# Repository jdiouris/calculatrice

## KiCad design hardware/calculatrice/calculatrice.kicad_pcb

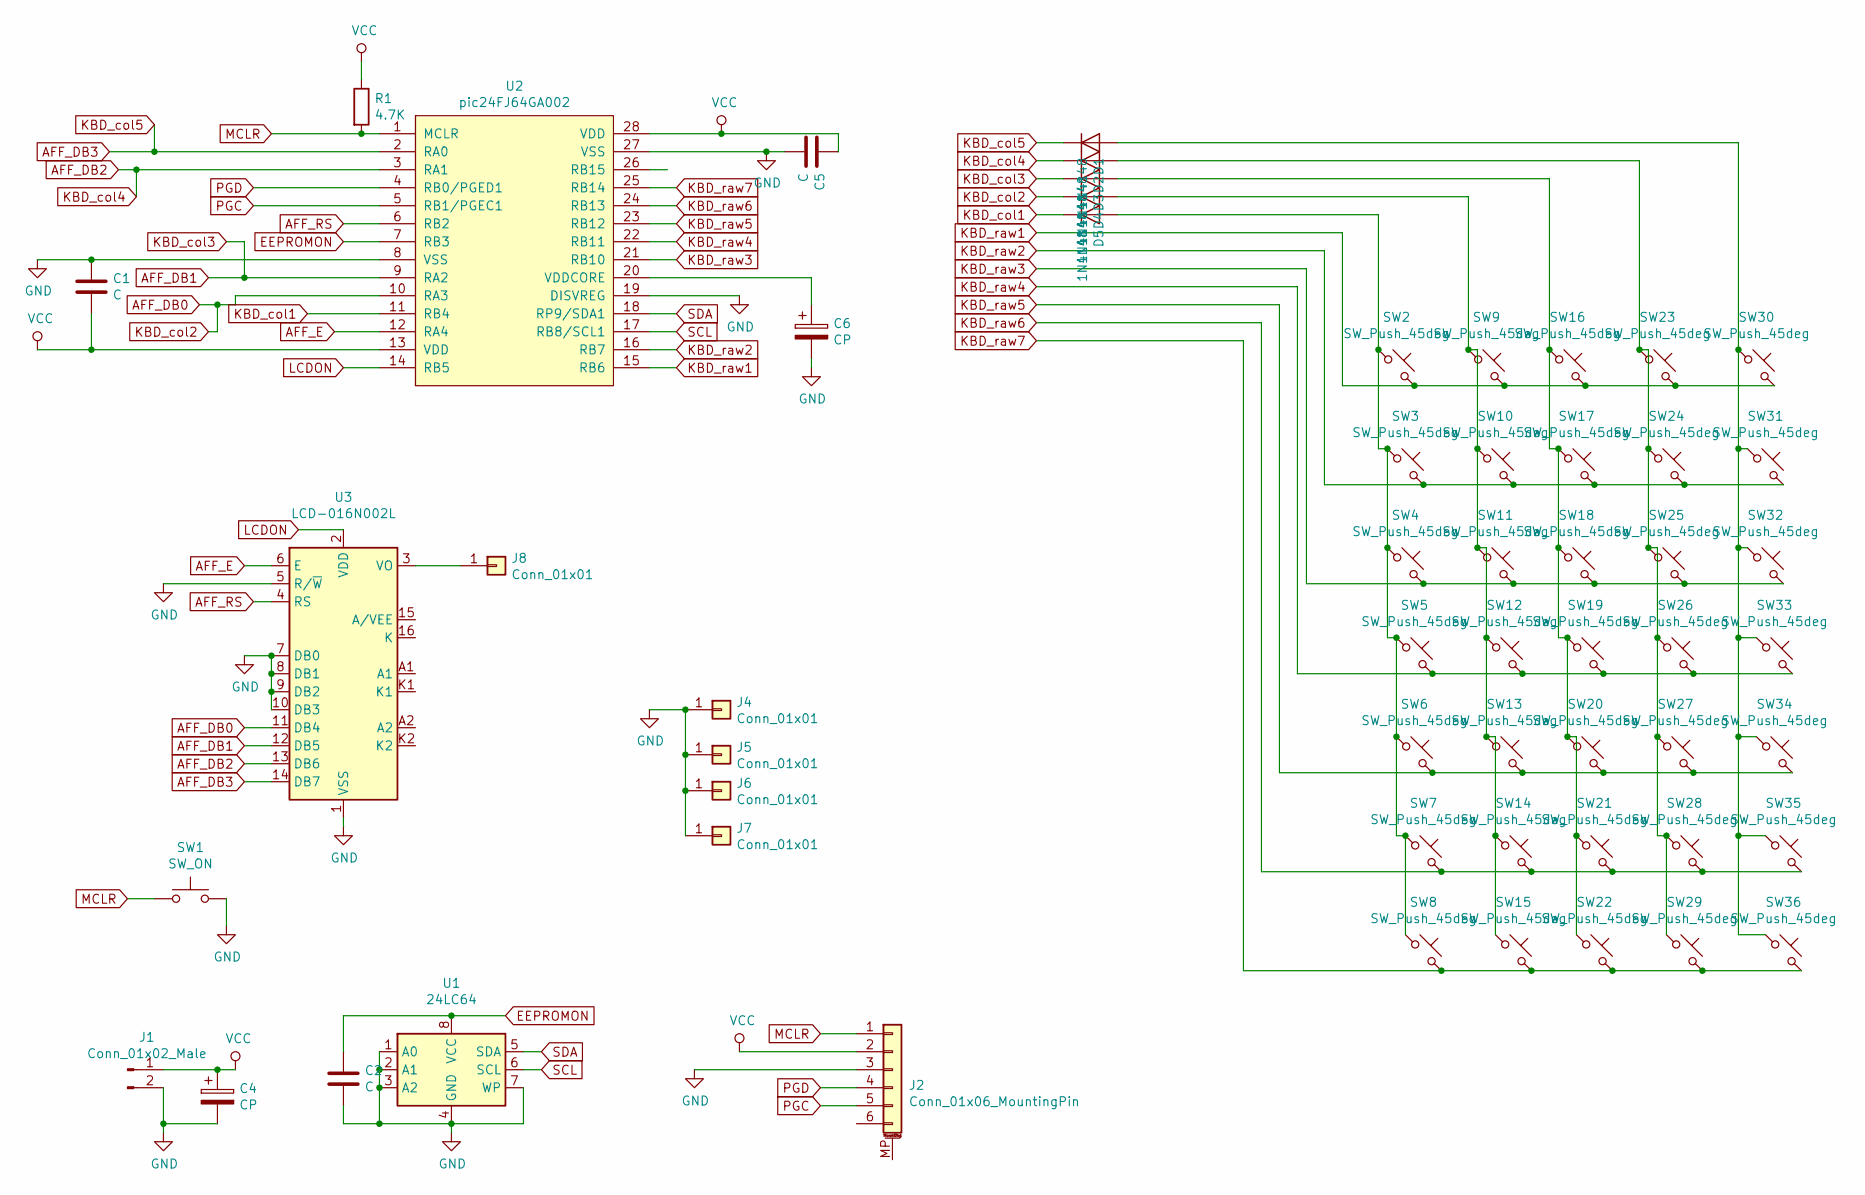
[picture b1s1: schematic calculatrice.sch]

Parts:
C1, C2, C5: C; C_Rect_L4_W2.5_P2.5
C4: CP; C_Rect_L4_W2.5_P2.5
C6: CP; C_Radial_D5_L6_P2.5
D1, D2, D3, D4, D5: 1N4148; D_DO-35_SOD27_P7.62mm_Horizontal
J1: Conn_01x02_Male; Pin_Header_Straight_1x02
J2: Conn_01x06_MountingPin; Pin_Header_Angled_1x06
J4, J5, J6, J7, J8: Conn_01x01; 1pin
R1: 4.7K; R3-LARGE_PADS
SW1: SW_ON; SW_PUSH-12mm
SW2, SW3, SW4, SW5, SW6, SW7, SW8, SW9, SW10, SW11, SW12, SW13, SW14, SW15, SW16, SW17, SW18, SW19, SW20, SW21, SW22, SW23, SW24, SW25, SW26, SW27, SW28, SW29, SW30, SW31, SW32, SW33, SW34, SW35, SW36: SW_Push_45deg; SW_PUSH-12mm
U1: 24LC64; DIP-8_W7.62mm_LongPads
U2: pic24FJ64GA002; DIP-28_W7.62mm_LongPads
U3: LCD-016N002L; LCD16

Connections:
AFF_DB0: D4.1 (K), U2.10 (RA3), U3.11 (DB4)
AFF_DB1: D3.1 (K), U2.9 (RA2), U3.12 (DB5)
AFF_DB2: D2.1 (K), U2.3 (RA1), U3.13 (DB6)
AFF_DB3: D1.1 (K), U2.2 (RA0), U3.14 (DB7)
AFF_E: U2.12 (RA4), U3.6 (E)
AFF_RS: U2.6 (RB2), U3.4 (RS)
EEPROMON: C2.1, U1.8 (VCC), U2.7 (RB3)
GND: C1.1, C2.2, C4.2, C5.2, C6.2, J1.2, J2.3, J4.1, J5.1, J6.1, J7.1, SW1.2, U1.1 (A0), U1.2 (A1), U1.3 (A2), U1.4 (GND), U1.7 (WP), U2.8 (VSS), U2.19 (DISVREG), U2.27 (VSS), U3.1 (VSS), U3.5 (R/~W), U3.7 (DB0), U3.8 (DB1), U3.9 (DB2), U3.10 (DB3)
KBD_col1: D5.1 (K), U2.11 (RB4)
KBD_raw1: SW2.2, SW9.2, SW16.2, SW23.2, SW30.2, U2.15 (RB6)
KBD_raw2: SW3.2, SW10.2, SW17.2, SW24.2, SW31.2, U2.16 (RB7)
KBD_raw3: SW4.2, SW11.2, SW18.2, SW25.2, SW32.2, U2.21 (RB10)
KBD_raw4: SW5.2, SW12.2, SW19.2, SW26.2, SW33.2, U2.22 (RB11)
KBD_raw5: SW6.2, SW13.2, SW20.2, SW27.2, SW34.2, U2.23 (RB12)
KBD_raw6: SW7.2, SW14.2, SW21.2, SW28.2, SW35.2, U2.24 (RB13)
KBD_raw7: SW8.2, SW15.2, SW22.2, SW29.2, SW36.2, U2.25 (RB14)
LCDON: U2.14 (RB5), U3.2 (VDD)
MCLR: J2.1, R1.2, SW1.1, U2.1 (MCLR)
unnamed: C6.1, U2.20 (VDDCORE)
unnamed: D1.2 (A), SW30.1, SW31.1, SW32.1, SW33.1, SW34.1, SW35.1, SW36.1
unnamed: D2.2 (A), SW23.1, SW24.1, SW25.1, SW26.1, SW27.1, SW28.1, SW29.1
unnamed: D3.2 (A), SW16.1, SW17.1, SW18.1, SW19.1, SW20.1, SW21.1, SW22.1
unnamed: D4.2 (A), SW9.1, SW10.1, SW11.1, SW12.1, SW13.1, SW14.1, SW15.1
unnamed: D5.2 (A), SW2.1, SW3.1, SW4.1, SW5.1, SW6.1, SW7.1, SW8.1
unnamed: J8.1, U3.3 (VO)
PGC: J2.5, U2.5 (RB1/PGEC1)
PGD: J2.4, U2.4 (RB0/PGED1)
SCL: U1.6 (SCL), U2.17 (RB8/SCL1)
SDA: U1.5 (SDA), U2.18 (RP9/SDA1)
VCC: C1.2, C4.1, C5.1, J1.1, J2.2, R1.1, U2.13 (VDD), U2.28 (VDD)

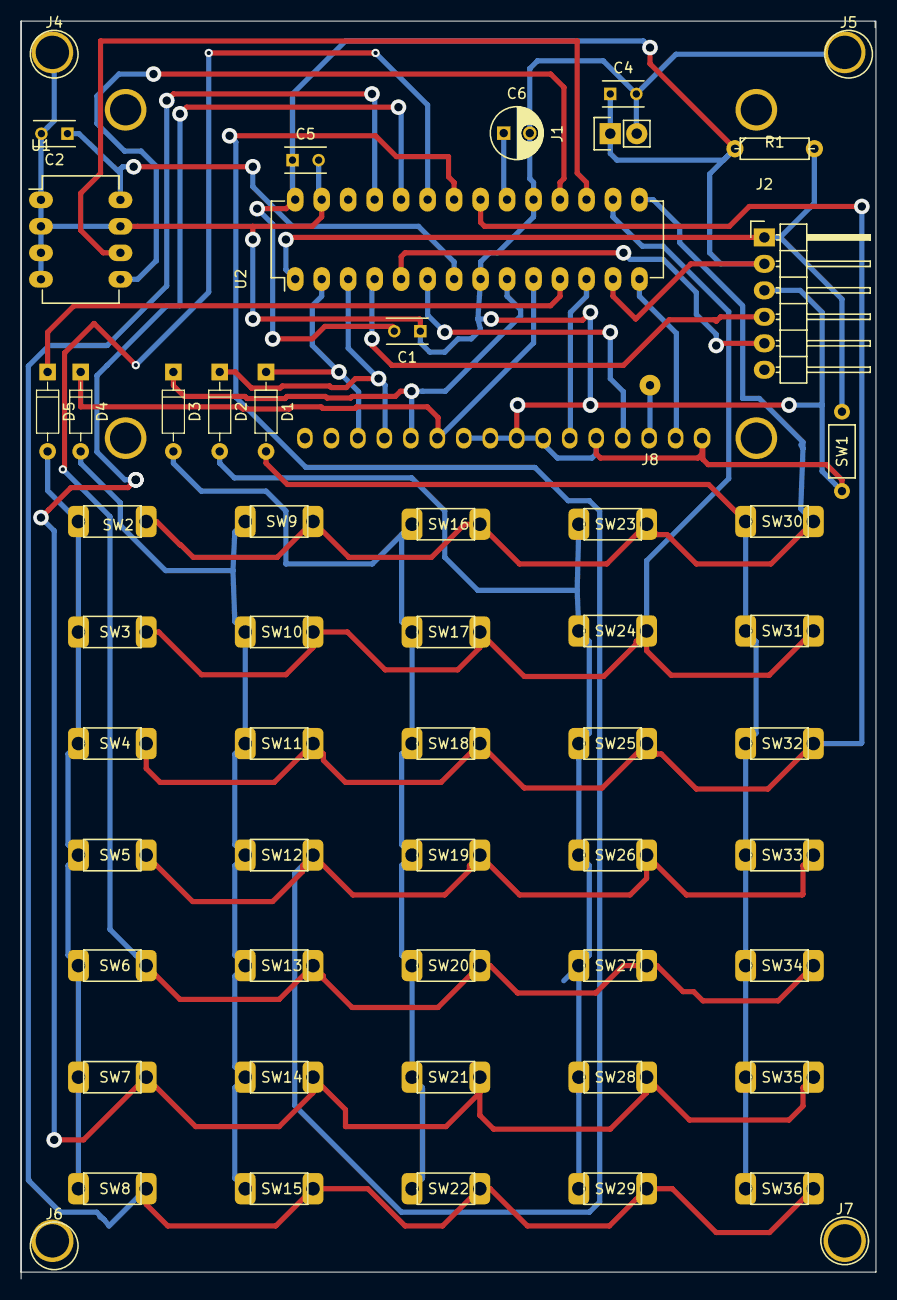
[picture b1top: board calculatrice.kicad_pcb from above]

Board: 2 copper layers, 82.0 x 120.7 mm, 57 parts (1 on the bottom side), 30 nets.

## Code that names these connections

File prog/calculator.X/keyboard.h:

/* 
 * File:   keyboard.h
 * Author: jeff
 *
 * Created on 2 janvier 2020, 18:11
 */

#ifndef KEYBOARD_H
#define	KEYBOARD_H

#define KBDCOL5 PORTAbits.RA0
#define KBDCOL4 PORTAbits.RA1
#define KBDCOL3 PORTAbits.RA2
#define KBDCOL2 PORTAbits.RA3
#define KBDCOL1 PORTBbits.RB4

#define KBDRAW1  PORTBbits.RB6
#define KBDRAW2  PORTBbits.RB7
#define KBDRAW3  PORTBbits.RB10
#define KBDRAW4  PORTBbits.RB11
#define KBDRAW5  PORTBbits.RB12
#define KBDRAW6  PORTBbits.RB13
#define KBDRAW7  PORTBbits.RB14


#define DIRKBDRAW1  TRISBbits.TRISB6
#define DIRKBDRAW2  TRISBbits.TRISB7
#define DIRKBDRAW3  TRISBbits.TRISB10
#define DIRKBDRAW4  TRISBbits.TRISB11
#define DIRKBDRAW5  TRISBbits.TRISB12
#define DIRKBDRAW6  TRISBbits.TRISB13
#define DIRKBDRAW7  TRISBbits.TRISB14

#define DIRKBCOL1  TRISBbits.TRISB4


#define PULLUPRB5  CNPU2bits.CN27PUE 
#define PULLUPRB6  CNPU2bits.CN24PUE 
#define PULLUPRB7  CNPU2bits.CN23PUE 
#define PULLUPRB8  CNPU2bits.CN22PUE
#define PULLUPRB9 CNPU2bits.CN21PUE
#define PULLUPRB10 CNPU2bits.CN16PUE
#define PULLUPRB11 CNPU1bits.CN15PUE
#define PULLUPRB12  CNPU1bits.CN14PUE 
#define PULLUPRB13 CNPU1bits.CN13PUE
#define PULLUPRB14  CNPU1bits.CN12PUE 
#define PULLUPRB15 CNPU1bits.CN11PUE


void initKbd()
{
    
    DIRKBDRAW1=1;
    DIRKBDRAW2=1;
    DIRKBDRAW3=1;
    DIRKBDRAW4=1;
    DIRKBDRAW5=1;
    DIRKBDRAW6=1;
    DIRKBDRAW7=1;
    
    DIRKBCOL1=0;  // Other are initialized for the LCD
    // Résistances pull-up
    PULLUPRB6=1;
    PULLUPRB7=1;
    PULLUPRB10=1;
    PULLUPRB11=1;
    PULLUPRB12=1;
    PULLUPRB13=1;
    PULLUPRB14=1;
}



int readRow()
{
    int row=0;
    if (KBDRAW1==0) row=1;
    if (KBDRAW2==0) row=2;
    if (KBDRAW3==0) row=3;
    if (KBDRAW4==0) row=4;
    if (KBDRAW5==0) row=5;
    if (KBDRAW6==0) row=6;
    if (KBDRAW7==0) row=7;
    return row;
}
void delayKbd()
{
   __delay_ms(10); 
}

int findKey()
{
    int key=0;
    int r;
    
    KBDCOL1=1;
    KBDCOL2=1;
    KBDCOL3=1;
    KBDCOL4=1;
    KBDCOL5=1;
    delayKbd();
    KBDCOL1=0;
    delayKbd();
    r=readRow();
    if (r!=0)
    {
       key=(r-1)*5+1; 
    }
    KBDCOL1=1;
    if (key==0)
    {
        KBDCOL2=0;
        delayKbd();
        r=readRow();
        if (r!=0)
        {
            key=(r-1)*5+2; 
        }  
    }
    KBDCOL2=1;
    if (key==0)
    {
        KBDCOL3=0;
        delayKbd();
        r=readRow();
        if (r!=0)
        {
            key=(r-1)*5+3; 
        }  
    }
    KBDCOL3=1;
    if (key==0)
    {
        KBDCOL4=0;
        delayKbd();
        r=readRow();
        if (r!=0)
        {
            key=(r-1)*5+4; 
        }  
    }
    KBDCOL4=1;
    if (key==0)
    {
        KBDCOL5=0;
        delayKbd();
        r=readRow();
        if (r!=0)
        {
            key=(r-1)*5+5; 
        }  
    }
   return key;
    
    
    
}

int readKey()
{
    int k=0;
    
    int key=findKey();
    if (key!=0)
    {
        // anti-rebond
       delayKbd();
        if (key==findKey()) 
        {
            k=key;
        }
    }
    
    return k;
}

int waitKey()
{
    int k=0;
    while (k==0) k=readKey();
    while (readKey()!=0);
    return k;
}

int testKeyC()
{
    int r;
    KBDCOL1=1;
    KBDCOL2=1;
    KBDCOL3=1;
    KBDCOL4=1;
    KBDCOL5=0;
   // delayKbd();
    r=readRow();
    //KBDCOL5=1;
    return (r!=0);
}

#endif	/* KEYBOARD_H */

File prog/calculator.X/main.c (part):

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#define FCY 8000000UL
#include <libpic30.h>

#define RS PORTBbits.RB2
#define EN PORTAbits.RA4
#define D4 PORTAbits.RA3
#define D5 PORTAbits.RA2
#define D6 PORTAbits.RA1
#define D7 PORTAbits.RA0

#define LCDON PORTBbits.RB5
#include "calculator.h"
#include "lcd.h"
#include "keyboard.h"
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void goSleep() {
    msg("Enter sleep mode...");
    __delay_ms(300);
    LCDON = 0;
    // TRISBbits.TRISB6=1.
    // CNEN1.CN14IE=1;
    // CNPU1.CN14PU1=1;
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    else wakeup = 0;

    // Start the LCD
    LCDON = 1;
    __delay_ms(100);
    // Initialise the Keyborad
    initKbd();
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
    //  printString("Enter sleep mode...");
    //  delay(1);
    //   LCDON = 0;
    //   TRISBbits.TRISB6=1.
    //   CNEN1.CN14IE=1;
    //   CNPU1.CN14PU1=1;
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
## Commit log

2020-01-26 Developpement
    RPN Calculator protptype
2020-02-14 menu of user Functions
2020-02-15 Function edit
2020-02-18 func edit
2020-02-18 fun edit
